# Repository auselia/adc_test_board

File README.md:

# ADS7057 test board (low-power 3.3 V version, v3)

The middle step between the perfboard and the AFE PCB. It takes the signal from the sensor, filters it, digitizes it with the ADS7057, and gives the SPI bus and two listener lines to a ZedBoard PMOD port. **It is powered only from the PMOD 3.3 V. There is no USB and no regulator.**

The 5 V / USB-C revision is kept in the git tag `v2-usb-5v`.

There are **two boards**, ordered separately:

| Board | What it is | Size |
|---|---|---|
| ADC test board (`ADC_Test`) | HPF, gain, LPF, driver, ADS7057, listener (WAKE_N, BIG_N), PMOD, bias-T for the head, current-measurement links, test points | **125 × 21.5 mm** |
| Sensor head (`ADC_Head`) | The perfboard charge amplifier on a PCB. The piezo wires solder to it. It is powered through the coax | 10 × 27 mm |

The head connects to **SENSOR IN (J1)** with one coax cable. The coax carries 3.3 V to the head (a bias-T) and the signal back. To use a function generator instead of the head, cut JP1.

The board is a narrow strip (21.5 mm) so that boards fit on adjacent PMOD ports (pitch about 22.7 mm). It is **always on**: the whole chain and the listener run all the time, and the listener only observes.

## What changed from v2 (5 V, USB-C)

| | v2 | v3 |
|---|---|---|
| Supply | USB-C or header, 5 V, SS14, ferrite, XC6206 for AVDD | **PMOD 3.3 V only**, through the 5-pin header J7 (jumper 1-2). AVDD through 10 Ω and 10 µF |
| Rails | 5 V, 2.3 V VMID5, 1.65 V VOCM | 3.3 V, **1.65 V** VMID5 and VOCM |
| Wake-up | LM393 window, trimmer RV1, nWAKE | **Listener**: passive 159 kHz high-pass, 723 kHz low-pass, two TLV7022 comparators. WAKE_N (35 mV) and BIG_N (111 mV) at SIG_IN, on PMOD pins 10 and 7. Observer only |
| Current measurement | none | J7: 4-wire source-measure unit connection (below). JP3 (capture rail) can be opened to measure or switch the chain alone |
| Test points | TP3 to TP20 on a bottom strip | TP3 to TP20 inside each block, names on the back |
| Size | 57 × 37.6 mm | 125 × 21.5 mm |
| Head | OPA365, 5 V from the coax | OPA365 at 3.3 V (V+ 2.9 V). Low-power option: OPA314 and Cf 220 pF on the same pads |

## Uses

The board serves two purposes. In the plant experiments, four boards sit on ZedBoard PMODs JA to JD: two control plants, one drying plant and one reference sensor. Each board is one channel. The listener lines tell the FPGA, next to the full waveform, how often a burst crosses a small or a large threshold. That data decides whether the battery product can run on a listener alone.

## Circuit

| Block | Parts | Values |
|---|---|---|
| High-pass filter | Sallen-Key, U1A | 100 pF C0G ×2, 10k, 20k: f0 = 113 kHz, Q = 0.71 |
| Gain | U1B | 1 + 3.9k/1k = 4.9 |
| Low-pass filter | Sallen-Key, U2A | 2.2k ×2, C1 = 2 × 100 pF, C2 = 100 pF: f0 = 512 kHz, Q = 0.71 |
| VMID5 (signal ground, half of +3V3_C, 1.65 V) | 10k/10k divider, U2B buffer | 10 Ω, 10 µF |
| Driver | THS4531, gain 1 | 1k in and feedback; VOCM = 1k/1k divider on AVDD |
| ADC input filter | | 10 Ω per leg, 4 × 100 pF C0G = 400 pF |
| AVDD (reference) | from +3V3_C through R34 10 Ω, C21 10 µF | 4.7 µF + 100 nF at the ADS7057 AVDD pin. RC corner 1.6 kHz |
| 3.3 V input | PMOD J3 pins 6 and 12 to J7 pin 1; J7 pins 2 and 3 are the board rail | C23 10 µF. No USB, no diode |
| Rail link | JP3 joins +3V3_C (U1, U2, U3, AVDD) to +3V3 (closed). The listener and DVDD are on +3V3 | Open JP3 to measure or switch the capture chain alone |
| MON output | 51 Ω from LPF_OUT to SMA J4 | The scope sees the same signal the ADC samples |
| Bias-T on SENSOR IN (J1) | JP1 (bridged), R26 47R + C32 10 µF, L2 470 µH, C33 100 nF, R27 1M | 3.3 V reaches the coax centre through 47 Ω and 470 µH. C33 passes the head signal to the filters |
| Listener filter | C40 100 pF + R35 10k (high-pass 159 kHz), R36 10k + C41 22 pF (low-pass 723 kHz) | Output LST, TP15. Gain 0.68 at 250 kHz (the filters load each other) |
| Listener thresholds | R21 1M, R22 33k, R39 15k, R40 15k, R41 33k, R23 1M from +3V3_L to ground; REFL = 1.65 V | WAKE_N ±24 mV and BIG_N ±76 mV at LST, which is 35 mV and 111 mV at SIG_IN (1.6 pC and 5.2 pC at Cf 47 pF) |
| Listener comparators | U6 (WAKE_N), U9 (BIG_N), TLV7022, 5 µA per channel, 260 ns | Open drain, 47k pull-ups R24 and R42 to 3.3 V |

Main board: 125 × 21.5 mm, 2 layers, all SMD parts on top, GND pour on both layers, 786 + 100 tracks.

### Sensor head

The perfboard circuit (TRL3 schematic), on its own board:

| Block | Parts | Values |
|---|---|---|
| Charge amplifier | U8 OPA365 (SOT-23-5) | 50 MHz, about 4.6 mA. Low-power option: OPA314 (3 MHz, 150 µA) with Cf 220 pF |
| Feedback | R28 1 MΩ, C34 47 pF C0G | Corner 3.4 kHz, gain 1/Cf |
| Reference | R29, R30 1M, C35 10 µF | VREF = V+/2, about 1.45 V |
| Output | R31 49.9 Ω, C38 100 nF | 50 Ω, AC-coupled onto the coax |
| Power from the coax | L1 470 µH, C36 100 nF, C37 10 µF | 3.3 V comes in on the coax centre. About 4.3 mA, V+ = 2.9 V |
| Piezo | TP1 (+, to the summing node), TP2 (−, to ground) | Two 1 mm holes. TP1 is on the centre line of the board and sets the piezo position |
| Output connector | J6 SMA, vertical | To SENSOR IN (J1) on the main board |

The bias-T at 3.3 V costs 0.17 dB at 250 kHz and 19 dB at 10 kHz (`python3 sim/head_bias_t.py 3.3`). The board is 22 mm long, not the 20 mm of the capsule drawing v3.

**Two head amplifiers.** The OPA365 is the lab default: it keeps the waveform faithful (noise gain 35 gives 1.4 MHz bandwidth) but draws 4.6 mA. The OPA314 draws 150 µA and fits the battery goal, but its 3 MHz gain-bandwidth needs Cf 220 pF (−3 dB near 360 kHz) and it has 14 nV/√Hz of noise against 4.5. Both are SOT-23-5 with the same pinout. Swap the amplifier and Cf.

## Silkscreen

| Label | What it is |
|---|---|
| SENSOR IN (J1) | SMA input for the sensor head. The centre pin carries 3.3 V while the jumper JP1 is bridged. Cut JP1 before you connect a function generator. |
| SCOPE OUT (J4) | SMA monitor output. It carries the same signal the ADC samples, through 51 Ω. Use a 1 MΩ scope input. A 50 Ω input halves the signal. |
| Test point names (back) | SIG_IN, HPF_OUT, GAIN_OUT, LPF_OUT, DRV_OUTP, DRV_OUTN, AINP, AINM, +3V3, AVDD, VMID5, VOCM, LST, WAKE_N, BIG_N, REFL, GND, GND |
| Silkscreen (top) | Test point numbers (TP3 to TP20) and IC numbers (U1 to U4, U6, U9); head: TP1, TP2, U8. Jumper names and PMOD pin legend on the back |
| PMOD pin list (back) | Pins used and their names |
| Leaf and waves (back) | Auselia mark |

Reference designators (R1, C4 and so on) are on the F.Fab layer, not on the silkscreen. Open the KiCad file to see them.

## Power

All power comes from the ZedBoard PMOD. J3 pins 6 and 12 carry 3.3 V and pins 5 and 11 carry GND. The ZedBoard feeds the PMOD connectors from its 3.3 V rail, rated 3 A and shared with the FMC and the other PMODs. This board draws about 27 mA, plus 5 mA for the head, so four boards are about 130 mA. Feed J7 instead (and cut JP6) to run on the bench.

J7 is a 5-pin header: 1 Onboard + (PMOD 3.3 V), 2 Force +, 3 Sense +, 4 Sense −, 5 Force −. Pins 2 and 3 are the board rail, pins 4 and 5 are ground. A jumper from pin 1 to pin 2 powers the board from the ZedBoard. To power it from a source-measure unit (for example a Keysight B2901BL) remove the jumper and connect Force to pins 2 and 5 and Sense to pins 3 and 4. The SMU then measures the total board current. JP3 (closed) joins the capture rail: open it to feed or switch U1, U2, U3 and AVDD separately. JP1 is the head power link.

AVDD is the ADC reference, and full scale is ±AVDD. It comes from the rail through 10 Ω and 10 µF. The ZedBoard 3.3 V noise is not known yet: probe TP11 and TP12.

The long-term product runs from a battery for a year. This board is the lab version. The listener (about 25 µA) and the OPA314 head (150 µA) are the building blocks for that, and the plan is in `doc/lowpower_plan.md`.

## Through-hole parts

JLCPCB solders these. They are in the BOM and the pick-and-place file.

| Ref | Part | LCSC |
|---|---|---|
| J1, J4 (and J6 on the head) | SMA jack, vertical, 5 pins (sensor in, MON, head out) | C496549 |
| J7 | 1×5 pin header, 2.54 mm (power / source-measure unit) | C492404 |
| J3 | 2×6 right-angle pin header, 2.54 mm | C60565 |

If JLCPCB declines a through-hole part, delete its line from the BOM and solder it yourself. The board has the same footprints either way.

## Connectors

- **J1 SENSOR IN:** SMA for the sensor head, carries +3.3 V on the centre pin (JP1 bridged).
- **J4 SCOPE OUT:** SMA monitor output, LPF_OUT through 51 Ω.
- **J7 header:** power and 4-wire SMU connection (jumper 1-2 for the PMOD supply).
- **H1, H2:** M3 mounting holes.
- **J3 PMOD:** 1 CS, 3 SDO, 4 SCLK, 5/11 GND, 6/12 3V3, 7 BIG_N, 10 WAKE_N.

All device ports are SMA female. Use one cable type everywhere (SMA male to male, RG316 or RG174, short): head to SENSOR IN, SENSOR IN to a generator, SCOPE OUT to the oscilloscope through an SMA male to BNC female adapter. The RP-SMA parts in some shops do not mate with these jacks. Connect the head to the oscilloscope only through the board, since the bias-T that powers the head is on the board.

Before you plug the board into JA–JD, check that pins 5/6 and 11/12 line up with GND/VCC on the ZedBoard silkscreen. Adjacent ports are about 22.7 mm apart and the board is 21.5 mm wide.

## SPI

- CS falling edge starts a conversion.
- Read 18 SCLK cycles on SDO. The frame is a leading 0, then D13..D0, then zeros (datasheet Fig. 1).
- Each frame returns the result of the **previous** conversion. The first frame after power-up returns all zeros.
- After power-up, send **24 SCLKs** in the first frame. That starts the offset calibration (datasheet 8.4.3.1), and SDO stays at zero. Then wait at least 95 ns before the next CS fall.
- Repeat the calibration when AVDD or the temperature changes a lot.
- SCLK can go up to 60 MHz. Start at 10–20 MHz.

## Cost (JLCPCB Economic PCBA, shipped to Chile)

The two boards are two JLCPCB orders (or one checkout with two designs). `python3 hw/tools/cost.py` prints the model. It is calibrated on the real quote of the first revision (2026-10-12, 5 boards, $114.36, no bias-T). The new parts have list prices from the JLCPCB library of 2026-10-15. The v2 numbers are estimates until you upload the files.

| Order | Goods (parts + PCB + fees) | Parts | Fees |
|---|---|---|---|
| ADC board × 2 | $66.84 | $32.20 | $30.64 |
| ADC board × 3 | $83.83 | $48.30 | $31.54 |
| ADC board × 5 | $117.82 | $80.50 | $33.33 |
| Sensor head × 5 | $40.77 | $15.65 | $21.12 |
| Sensor head × 10 | $57.94 | $31.29 | $22.65 |

Both orders together, with shipping (Global Standard $10.75 per parcel) and 19 % IVA:

| | One parcel | Two parcels |
|---|---|---|
| 2 ADC boards + 5 heads | $140.84 | $153.64 |
| 2 ADC boards + 10 heads | $161.46 | $174.26 |

- The head's fixed fees (setup $8.24, stencil $1.55, hand-solder labor $3.61, PCB $4.00, one more extended type) are about $20 per order. A single panel would save them, but it forces equal quantities and mouse-bite tabs. Two orders let you buy 2 ADC boards and 10 heads.
- The OPA365 ($2.67) is the most expensive part of a head. The OPA2365 (SOIC-8) would be $1.38 and needs no new extended fee, but it does not fit in 10 mm × 27 mm with the SMA.
- DHL Express costs about $32 more per parcel (3–7 days).
- "Confirm Parts Placement" adds $0.45 per order.

First revision, real quote for 5 boards (no head, no bias-T):

| Item | Price |
|---|---|
| PCB, 5 pcs, 2 layers, HASL with lead, 24 h build | $4.00 |
| Components, 27 part types | $80.14 |
| Setup fee | $8.24 |
| Stencil | $1.55 |
| Extended components fee, 4 types | $12.36 |
| SMT assembly | $1.32 |
| Hand-soldering labor | $3.61 |
| Manual assembly, through-hole joints | $2.23 |
| Nitrogen reflow | $0.91 |
| **Order total** | **$114.36** |

The ADS7057 pays no X-ray fee in Economic assembly. The through-hole part types (SMA, headers, trimmer) pay no extended-part fee.

> The model is calibrated on the first quote. A real quote of this revision (2026-10-15, 5 ADC boards, 5 heads, one checkout) showed merchandise $159.73 and shipping $52.45 because the cart was above $150. Split it in two orders (Global Standard $10.75 each) to stay below that line.

## JLCPCB placement check

The JLCPCB viewer showed four problems on the first revision, and the CPL corrects them. **New parts are not checked yet:** U6 and U9 (TLV7022, SOT-23-8), U8 (SOT-23-5, head), L1 and L2 (1210 inductors), J6 (SMA). Look at them in the viewer.

| Part | Problem | CPL rotation |
|---|---|---|
| J7 (1×5 header) | Rotation as in the CPL (90), not checked in the viewer | check |
| J3 (2×6 header) | Row horizontal, pads vertical | 0 → 90 |

J3 and J7 have their origin on pin 1 in the KiCad footprint, so they are placed by that pin.

## Verification

| Check | Status | Result |
|---|---|---|
| ERC, DRC, schematic-to-board parity | Done | 0 errors, 0 unconnected, 0 mismatches |
| Pinouts and polarity against the datasheets | Done | All ICs, SS14 |
| JLCPCB placement viewer | **Open** for U6, U9, U8, L1, L2, J6 | 2 rotations fixed. Check again after the new CPL |
| DC bias, AC response, noise | Done | Table below |
| Tolerance Monte Carlo, 150 runs | Done | 10 kHz loss under 40 dB in 11 of 150 runs |
| 250 kHz burst, headroom at 3.3 V | Done | A 120 mV event reaches 16 % of full scale. Clipping starts near 0.37 V (`doc/data/sim.json`) |
| As-built netlist, rails to listener | Done | `python3 sim/netlist_verify.py`: 18 DC checks, gains and bursts all pass. It found that the first listener filter passed only 0.45 of the signal, which was fixed (R36, C41, R39, R40) |
| Listener on 25 real captures | Done | 7 of 7 events above WAKE_N, none of the 18 noise captures (peak 26 mV against 35 mV). Rate of false alarms per hour is open (`sim/g1_listener.py`) |
| ADC input settling | Done | 30 to 55 ns against 95 ns minimum |
| Cable on the SCOPE OUT SMA | Done | No peaking up to 5 nF |
| THS4531 into 10 Ω and 400 pF | **Open** | TI's model fails in ngspice and LTspice batch mode does not run here. `sim/ths4531_stability_estimate.py` gives 48 to 77° of margin for assumed output impedances. Run `sim/ltspice/ths4531_cap_load.cir` in LTspice |
| Head and bias-T, ngspice with the OPA365 model | Done | 0.17 dB loss at 250 kHz, 19 dB at 10 kHz, about 4.3 mA at 3.3 V. `python3 sim/head_bias_t.py 3.3` |
| ZedBoard 3.3 V rail noise | **Open** | Probe TP11 and TP12 with the board plugged in |
| Adjacent PMOD ports (22.7 mm) | **Open** | Print 1:1 and test |
| Head board, DRC | Done | 0 unconnected, no electrical errors. Two courtyard overlaps (TP/L1 and C34/R28) |
| Head: piezo wires, strain relief, RTV | Open | Mechanical, on the bench |
| Print the PCB 1:1 and test-fit parts | Open | |
| Fit on the ZedBoard PMOD | Open | |
| Bench bring-up | Open | See below |

`sim/vendor_chain.py` runs the checks and `sim/vendor_results.txt` holds the output. The OPA365 is TI's own model. The THS4531 is a datasheet-based model (27 MHz, 2.5 Ω), because TI's model gives a −3 dB point at 17 kHz in ngspice. The ADC input is the datasheet model: 50 Ω and 16 pF per leg. Run `python3 sim/models/fetch_models.py` to download the TI models, which are not stored in the repo.

| Result | Value | Target |
|---|---|---|
| DC points | VMID5 1.65 V, VOCM 1.65 V, ADC inputs 1.65 V | |
| Gain at 250 kHz, SMA to ADC | 12.2 dB (×4.1) | |
| Flatness 230 to 280 kHz | 0.08 dB | < 1 dB |
| Loss at 10 kHz, re 250 kHz | 40.5 dB, worst of 150 runs 39.7 dB | ≥ 40 dB |
| Loss at 2 MHz | 24.0 dB | ≥ 20 dB |
| −3 dB band | 106 to 502 kHz | |
| Board noise at the ADC | 77 µV rms, 0.2 LSB | |

Things the simulation does not cover:

- THS4531 stability with the 400 pF load. TI's guidance is a 2 pF differential load without an isolation resistor, so 20 Ω and 400 pF needs a measurement. If it rings, raise R16 and R17 from 10 Ω to 20 or 30 Ω.
- Temperature and the noise of a real power bank.
- Layout coupling and the real ZedBoard supply.

Paper checks:

- The chain was simulated at 3.3 V (`sim/vendor_chain.py`, `sim/g1_chain33.py`).
- The board draws about 27 mA plus 5 mA for the head, about 0.1 W.

## Bring-up

With the sensor head: connect it to J1 with the coax, power the board from the PMOD (or J7 at 3.3 V), and the head runs from the rail (about +4.3 mA). Measure about 2.9 V on C37 and 1.45 V on the OPA365 output, VREF and C35. Then continue from step 3.

1. Remove the J7 jumper and feed pins 2 and 5 with 3.3 V and a 100 mA limit (SMU Force), Sense on pins 3 and 4. Check +3V3 (3.30 V), AVDD (3.30 V), VOCM (1.65 V), VMID5 (1.65 V) and REFL (1.65 V) at the test points before the PMOD connects. Then fit the jumper 1-2 and connect the PMOD.
2. Plug the board into the ZedBoard and check that WAKE_N and BIG_N read high (3.3 V).
3. Feed J1 from the Analog Discovery 2 with a 250 kHz, 100 mV sine. Compare SCOPE OUT with the input on the scope (1 MΩ input).
4. Read SPI codes. Check the idle code and the amplitude against the scope.
5. Sweep 10 kHz to 2 MHz and compare with the table above. The 10 kHz loss is the thinnest margin.
6. Raise a 250 kHz burst from 10 mV: WAKE_N must drop near 35 mV and BIG_N near 111 mV at J1 (±12 mV from the comparator offset). Log TP15 to TP18 on the scope.
7. With the SMU on J7, read the total current (about 25 mA). Open JP3 to read the capture chain and the listener separately.

## Manual (`doc/`)

`doc/ADS7057_test_board_hardware_manual_letter_v0.3.pdf` explains the boards in 54 steps plus the sensor head: the basics, every block, the layout, the order and the bring-up. Two print versions (`_print`, `_print_duplex`) have a 14 mm binding margin.

Rebuild: `M4_PDF_PYTHON=<python with pymupdf> python3 doc/tools/make_adc_manual.py`. The figures read `doc/data/board.json` and `doc/data/sim.json`, made by `doc/tools/export_board.py` (KiCad python) and `doc/tools/export_sim.py`.

## Files (`hw/`)

- `ADC_Test.kicad_pro/.kicad_sch`: the KiCad 10 project and the schematic of both boards.
- `ADC_Test.kicad_pcb`: main board. `ADC_Head.kicad_pcb`: sensor head. Both are built from the same netlist.
- `ADC_Test_schematic.pdf`: the schematic.
- `fab/ADC_Test_gerbers.zip`, `fab/ADC_Head_gerbers.zip`: Gerbers and drill files.
- `fab/ADC_*_BOM_JLC.csv` and `fab/ADC_*_CPL_JLC.csv`: BOM and pick-and-place for each board.
- `preview/`: renders and the 1:1 print PDFs of both boards.
- DRC: main board 0 errors and 0 unconnected (the parity warnings are the head parts, which are not on this board). Head board 0 unconnected, two courtyard warnings.

## Rebuild

```
python3 hw/tools/design.py hw          # schematic (then export netlist with kicad-cli)
NOPLANE=1 FREEROUTING=/path/to/freerouting hw/tools/route.sh 60   # place (layout_v3.py), route, finish
BOARD=head FREEROUTING=/path/to/freerouting hw/tools/route.sh 60   # the sensor head
hw/tools/drc.sh; BOARD=head hw/tools/drc.sh
hw/tools/fab.sh && BOARD=adc python3 hw/tools/jlc_files.py && BOARD=head python3 hw/tools/jlc_files.py
```

Freerouting 2.4.1 needs Java 25 (the macOS .dmg bundles it).

## At JLCPCB checkout

- Two orders: upload `ADC_Test_*` and `ADC_Head_*` separately.
- Upload the new CPL, then open Component Placements and check U6, U9 (pin 1), J7 and J3 (see "JLCPCB placement check"). On the head also check U8 pin 1, L1, J6.
- Look at J1, J4 and J6 as well. The SMA model looked offset against its four legs.
- Check pin 1 of U4 (ADS7057) in particular.

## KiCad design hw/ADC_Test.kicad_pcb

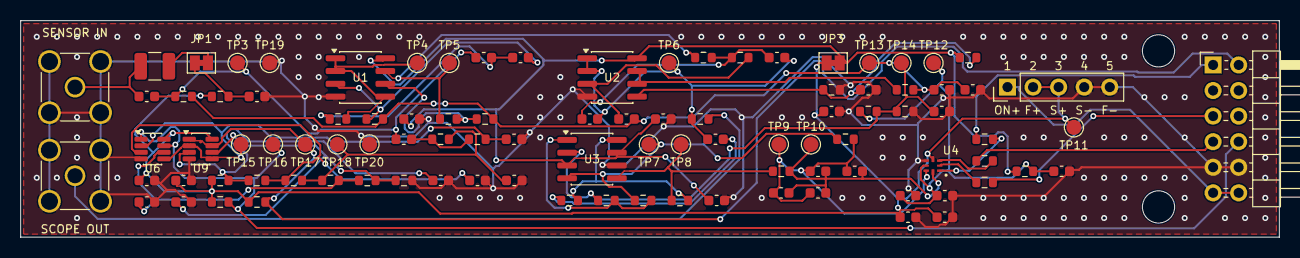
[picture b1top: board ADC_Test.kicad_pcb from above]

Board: 2 copper layers, 125.0 x 21.5 mm, 101 parts (0 on the bottom side), 44 nets.

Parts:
C1, C2, C4, C5, C6, C14, C15, C16, C17, C40: 100pF C0G; C_0603_1608Metric
C3, C9, C10, C12, C20, C22, C26, C27, C28, C33, C43, C44, C45: 100nF; C_0603_1608Metric
C7, C11, C13, C19, C42: 1uF; C_0603_1608Metric
C8, C21, C23, C32: 10uF; C_0603_1608Metric
C18: 4.7uF; C_0603_1608Metric
C41: 22pF C0G; C_0603_1608Metric
H1, H2: M3; MountingHole_3.2mm_M3
J1: SMA SENSOR IN; SMA_Amphenol_132134-11_Vertical
J3: PMOD (ZedBoard); PinHeader_2x06_P2.54mm_Horizontal
J4: SMA MON; SMA_Amphenol_132134-11_Vertical
J7: POWER / SMU; PinHeader_1x05_P2.54mm_Vertical
JP1: HEAD PWR; SolderJumper-2_P1.3mm_Bridged_Pad1.0x1.5mm
JP3: CAPTURE LINK; SolderJumper-2_P1.3mm_Bridged_Pad1.0x1.5mm
L2: 470uH; L_1210_3225Metric
R1, R7, R8, R35, R36: 10k; R_0603_1608Metric
R2: 20k; R_0603_1608Metric
R3: 3.9k; R_0603_1608Metric
R4, R10, R11, R12, R13, R14, R15: 1.00k; R_0603_1608Metric
R5, R6: 2.2k; R_0603_1608Metric
R9, R16, R17, R34: 10R; R_0603_1608Metric
R18, R19, R20: 22R; R_0603_1608Metric
R21, R23, R27: 1M; R_0603_1608Metric
R22, R41: 33k; R_0603_1608Metric
R24, R42: 47k; R_0603_1608Metric
R25: 51R; R_0603_1608Metric
R26: 47R; R_0603_1608Metric
R39, R40: 15k; R_0603_1608Metric
TP3: SIG_IN; TestPoint_Pad_D1.5mm
TP4: HPF_OUT; TestPoint_Pad_D1.5mm
TP5: GAIN_OUT; TestPoint_Pad_D1.5mm
TP6: LPF_OUT; TestPoint_Pad_D1.5mm
TP7: DRV_OUTP; TestPoint_Pad_D1.5mm
TP8: DRV_OUTN; TestPoint_Pad_D1.5mm
TP9: AINP; TestPoint_Pad_D1.5mm
TP10: AINM; TestPoint_Pad_D1.5mm
TP11: +3V3; TestPoint_Pad_D1.5mm
TP12: AVDD; TestPoint_Pad_D1.5mm
TP13: VMID5; TestPoint_Pad_D1.5mm
TP14: VOCM; TestPoint_Pad_D1.5mm
TP15: LST; TestPoint_Pad_D1.5mm
TP16: WAKE_N; TestPoint_Pad_D1.5mm
TP17: BIG_N; TestPoint_Pad_D1.5mm
TP18: REFL; TestPoint_Pad_D1.5mm
TP19, TP20: GND; TestPoint_Pad_D1.5mm
U1, U2: OPA2365; SOIC-8_3.9x4.9mm_P1.27mm
U3: THS4531; SOIC-8_3.9x4.9mm_P1.27mm
U4: ADS7057; ADS7057_X2QFN-8_1.5x1.5mm
U6, U9: TLV7022; SOT-23-8

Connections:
+3V3: C19.1, C20.1, C23.1, C28.1, C45.1, J7.2, J7.3, JP3.1, R21.1, R24.1, R26.1, R42.1, TP11.1, U4.4, U6.8, U9.8
+3V3_C: C3.1, C10.1, C12.1, JP3.2, R7.1, R34.1, U1.8, U2.8, U3.3, U3.7
+3V3_PMOD: J3.11, J3.12, J7.1
AINM: C14.2, C15.2, C16.2, C17.2, R17.2, TP10.1, U4.8
AINP: C14.1, C15.1, C16.1, C17.1, R16.2, TP9.1, U4.7
AVDD: C18.1, C21.1, C22.1, R14.1, R34.2, TP12.1, U4.6
BIG_N: J3.2, R42.2, TP17.1, U9.1, U9.7
CS: J3.1, R18.1
CS_A: R18.2, U4.1
DRV_A: C11.2, R10.1
DRV_INN: R11.2, R12.2, U3.1
DRV_INP: R10.2, R13.2, U3.8
DRV_OUTN: R13.1, R17.1, TP8.1, U3.5
DRV_OUTP: R12.1, R16.1, TP7.1, U3.4
GAIN_OUT: R3.1, R5.1, TP5.1, U1.7
GND: C3.2, C7.2, C8.2, C9.2, C10.2, C12.2, C13.2, C18.2, C19.2, C20.2, C21.2, C22.2, C23.2, C26.2, C27.2, C28.2, C32.2, C41.2, C42.2, C43.2, C44.2, C45.2, J1.2, J3.9, J3.10, J4.2, J7.4, J7.5, R8.2, R15.2, R23.2, TP19.1, TP20.1, U1.4, U2.4, U3.6, U4.5, U6.4, U9.4
GN_FB: R3.2, R4.1, U1.6
HEAD_LINE: C33.1, J1.1, L2.1
HEAD_PWR: C32.1, JP1.1, R26.2
HEAD_PWR_L: JP1.2, L2.2
HPF_OUT: R1.2, TP4.1, U1.1, U1.2, U1.5
HP_A: C1.2, C2.1, R1.1
HP_B: C2.2, R2.1, U1.3
LPF_OUT: C4.2, C5.2, C11.1, R25.1, TP6.1, U2.1, U2.2
LP_A: C4.1, C5.1, R5.2, R6.1
LP_B: C6.1, R6.2, U2.3
LST: C41.1, R36.2, TP15.1, U6.2, U6.5, U9.2, U9.5
LST_A: C40.2, R35.1, R36.1
MON: J4.1, R25.2
REFL: C42.1, R35.2, R39.2, R40.1, TP18.1
SCLK: J3.7, R19.1
SCLK_A: R19.2, U4.3
SDO: J3.5, R20.2
SDO_A: R20.1, U4.2
SIG_IN: C1.1, C33.2, C40.1, R27.1, TP3.1
TH1M: C27.1, R40.2, R41.1, U6.6
TH1P: C26.1, R22.2, R39.1, U6.3
TH2M: C44.1, R23.1, R41.2, U9.6
TH2P: C43.1, R21.2, R22.1, U9.3
VMID5: C6.2, C8.1, C9.1, R2.2, R4.2, R9.2, R27.2, TP13.1
VMID_BUF: R9.1, U2.6, U2.7
VMID_DIV: C7.1, R7.2, R8.1, U2.5
VOCM: C13.1, R11.1, R14.2, R15.1, TP14.1, U3.2
WAKE_N: J3.8, R24.2, TP16.1, U6.1, U6.7

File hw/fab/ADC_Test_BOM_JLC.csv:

Comment,Designator,Footprint,LCSC Part #
100pF C0G,"C1,C2,C4,C5,C6,C14,C15,C16,C17,C40",C_0603_1608Metric,C14858
100nF,"C3,C9,C10,C12,C20,C22,C26,C27,C28,C33,C43,C44,C45",C_0603_1608Metric,C14663
1uF,"C7,C11,C13,C19,C42",C_0603_1608Metric,C15849
10uF,"C8,C21,C23,C32",C_0603_1608Metric,C19702
4.7uF,C18,C_0603_1608Metric,C19666
22pF C0G,C41,C_0603_1608Metric,C1653
SMA jack,"J1,J4",SMA_Amphenol_132134-11_Vertical,C496549
Header 2x6 right angle,J3,PinHeader_2x06_P2.54mm_Horizontal,C60565
Header 1x5,J7,PinHeader_1x05_P2.54mm_Vertical,C492404
470uH,L2,L_1210_3225Metric,C75644
10k,"R1,R7,R8,R35,R36",R_0603_1608Metric,C25804
20k,R2,R_0603_1608Metric,C4184
3.9k,R3,R_0603_1608Metric,C23018
1.00k,"R4,R10,R11,R12,R13,R14,R15",R_0603_1608Metric,C21190
2.2k,"R5,R6",R_0603_1608Metric,C4190
10R,"R9,R16,R17,R34",R_0603_1608Metric,C22859
22R,"R18,R19,R20",R_0603_1608Metric,C23345
1M,"R21,R23,R27",R_0603_1608Metric,C22935
33k,"R22,R41",R_0603_1608Metric,C4216
47k,"R24,R42",R_0603_1608Metric,C25819
51R,R25,R_0603_1608Metric,C23197
47R,R26,R_0603_1608Metric,C23182
15k,"R39,R40",R_0603_1608Metric,C22809
OPA2365,"U1,U2",SOIC-8_3.9x4.9mm_P1.27mm,C130011
THS4531,U3,SOIC-8_3.9x4.9mm_P1.27mm,C705347
ADS7057,U4,ADS7057_X2QFN-8_1.5x1.5mm,C2669902
TLV7022,"U6,U9",SOT-23-8,C2862588

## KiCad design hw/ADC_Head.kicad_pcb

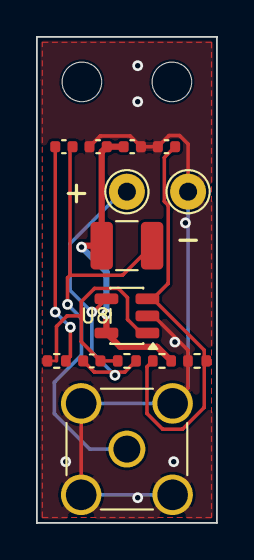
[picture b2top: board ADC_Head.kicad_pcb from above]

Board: 2 copper layers, 10.0 x 27.0 mm, 16 parts (0 on the bottom side), 7 nets.

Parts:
C34: 47pF C0G; C_0402_1005Metric
C35, C37: 10uF; C_0402_1005Metric
C36, C38: 100nF; C_0402_1005Metric
H3, H4: M2; MountingHole_2.2mm_M2
J6: SMA HEAD OUT; SMA_Amphenol_132134-11_Vertical
L1: 470uH; L_1210_3225Metric
R28, R29, R30: 1M; R_0402_1005Metric
R31: 49.9R; R_0402_1005Metric
TP1: PIEZO +; TestPoint_THTPad_D2.0mm_Drill1.0mm
TP2: PIEZO -; TestPoint_THTPad_D2.0mm_Drill1.0mm
U8: OPA365; SOT-23-5

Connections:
HAC: C38.1, R31.2
HGND: C35.2, C36.2, C37.2, J6.2, R30.2, TP2.1, U8.2
HLINE: C38.2, J6.1, L1.1
HOUT: C34.2, R28.2, R31.1, U8.1
HREF: C35.1, R29.2, R30.1, U8.3
HSUM: C34.1, R28.1, TP1.1, U8.4
HV: C36.1, C37.1, L1.2, R29.1, U8.5

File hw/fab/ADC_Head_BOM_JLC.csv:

Comment,Designator,Footprint,LCSC Part #
47pF C0G,C34,C_0402_1005Metric,C1567
10uF,"C35,C37",C_0402_1005Metric,C15525
100nF,"C36,C38",C_0402_1005Metric,C307331
SMA jack,J6,SMA_Amphenol_132134-11_Vertical,C496549
470uH,L1,L_1210_3225Metric,C75644
1M,"R28,R29,R30",R_0402_1005Metric,C26083
49.9R,R31,R_0402_1005Metric,C25120
OPA365,U8,SOT-23-5,C96626

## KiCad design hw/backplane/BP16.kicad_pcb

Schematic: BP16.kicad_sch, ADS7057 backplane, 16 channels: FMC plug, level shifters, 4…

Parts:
C1, C2, C3, C4, C5, C6, C7, C8, C9, C10, C11, C12, C13, C14, C15, C16, C18, C20, C22, C24, C26, C28, C30, C32, C34, C36, C38, C40, C42, C44, C46, C48, C50, C51, C52, C54, C58: 100nF; C_0603_1608Metric; LCSC C14663
C17, C19, C21, C23, C25, C27, C29, C31, C33, C35, C37, C39, C41, C43, C45, C47, C49: 10uF; C_0603_1608Metric; LCSC C19702
C53, C55, C56, C57: 22uF 25V; C_0805_2012Metric; LCSC C45783
C59, C60: 10nF; C_0603_1608Metric; LCSC C57112
D1: SS14; D_SMA; LCSC C2480
D2: 3V3 OK; LED_0603_1608Metric; LCSC C2286
H1, H2, H3, H4, H5, H6: M3; MountingHole_3.2mm_M3
J1: ASP-134602-01; ASP-134602-01_LPC; LCSC C2875619
J2: SLOT 0; PinSocket_2x06_P2.54mm_Vertical; LCSC C36191
J3: SLOT 1; PinSocket_2x06_P2.54mm_Vertical; LCSC C36191
J4: SLOT 2; PinSocket_2x06_P2.54mm_Vertical; LCSC C36191
J5: SLOT 3; PinSocket_2x06_P2.54mm_Vertical; LCSC C36191
J6: SLOT 4; PinSocket_2x06_P2.54mm_Vertical; LCSC C36191
J7: SLOT 5; PinSocket_2x06_P2.54mm_Vertical; LCSC C36191
J8: SLOT 6; PinSocket_2x06_P2.54mm_Vertical; LCSC C36191
J9: SLOT 7; PinSocket_2x06_P2.54mm_Vertical; LCSC C36191
J10: SLOT 8; PinSocket_2x06_P2.54mm_Vertical; LCSC C36191
J11: SLOT 9; PinSocket_2x06_P2.54mm_Vertical; LCSC C36191
J12: SLOT 10; PinSocket_2x06_P2.54mm_Vertical; LCSC C36191
J13: SLOT 11; PinSocket_2x06_P2.54mm_Vertical; LCSC C36191
J14: SLOT 12; PinSocket_2x06_P2.54mm_Vertical; LCSC C36191
J15: SLOT 13; PinSocket_2x06_P2.54mm_Vertical; LCSC C36191
J16: SLOT 14; PinSocket_2x06_P2.54mm_Vertical; LCSC C36191
J17: SLOT 15; PinSocket_2x06_P2.54mm_Vertical; LCSC C36191
J18: 5 V IN; TerminalBlock_Phoenix_MKDS-1,5-2-5.08_1x02_P5.08mm_Horizont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; LCSC C8465
R1, R2, R3, R4, R5, R6, R7, R8, R9, R10, R11, R12, R13, R14, R15, R16, R17, R18, R19, R20, R21, R22, R23, R24, R25, R26, R27, R28, R29, R30, R31, R32, R33, R34, R35, R36, R37, R38, R39, R40, R41, R42, R43, R44, R45, R46, R47, R48, R49, R50, R51, R52, R53, R54, R55, R56: 100k; R_0603_1608Metric; LCSC C25803
R57, R58, R59, R60, R61, R62, R63, R64, R65, R66, R67, R68, R69, R70, R71, R72: 22R; R_0603_1608Metric; LCSC C23345
R73: 1k; R_0603_1608Metric; LCSC C21190
TP1: +3V3; TestPoint_Pad_D1.5mm
TP2: GND; TestPoint_Pad_D1.5mm
TP3: +5V; TestPoint_Pad_D1.5mm
TP4: VADJ; TestPoint_Pad_D1.5mm
U1, U2, U3, U4, U5, U6, U7, U8: SN74LVC8T245; TSSOP-24_4.4x7.8mm_P0.65mm; LCSC C27643
U9, U10: SN74LVC244A; TSSOP-20_4.4x6.5mm_P0.65mm; LCSC C7668
U11: TPS7A8300; QFN-20-1EP_3.5x3.5mm_P0.5mm_EP2x2mm; LCSC C544500

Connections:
+3V3: C2.1, C4.1, C6.1, C8.1, C10.1, C12.1, C14.1, C16.1, C19.1, C20.1, C21.1, C22.1, C23.1, C24.1, C25.1, C26.1, C27.1, C28.1, C29.1, C30.1, C31.1, C32.1, C33.1, C34.1, C35.1, C36.1, C37.1, C38.1, C39.1, C40.1, C41.1, C42.1, C43.1, C44.1, C45.1, C46.1, C47.1, C48.1, C49.1, C50.1, C51.1, C52.1, C55.1, C56.1, C57.1, C58.1, C60.1, J2.11, J2.12, J3.11, J3.12, J4.11, J4.12, J5.11, J5.12, J6.11, J6.12, J7.11, J7.12, J8.11, J8.12, J9.11, J9.12, J10.11, J10.12, J11.11, J11.12, J12.11, J12.12, J13.11, J13.12, J14.11, J14.12, J15.11, J15.12, J16.11, J16.12, J17.11, J17.12, R9.1, R10.1, R11.1, R12.1, R13.1, R14.1, R15.1, R16.1, R17.1, R18.1, R19.1, R20.1, R21.1, R22.1, R23.1, R24.1, R25.1, R26.1, R27.1, R28.1, R29.1, R30.1, R31.1, R32.1, R33.1, R34.1, R35.1, R36.1, R37.1, R38.1, R39.1, R40.1, R41.1, R42.1, R43.1, R44.1, R45.1, R46.1, R47.1, R48.1, R49.1, R50.1, R51.1, R52.1, R53.1, R54.1, R55.1, R56.1, R73.1, TP1.1, U1.23 (VCCB), U1.24 (VCCB), U2.23 (VCCB), U2.24 (VCCB), U3.23 (VCCB), U3.24 (VCCB), U4.23 (VCCB), U4.24 (VCCB), U5.23 (VCCB), U5.24 (VCCB), U6.23 (VCCB), U6.24 (VCCB), U7.23 (VCCB), U7.24 (VCCB), U8.23 (VCCB), U8.24 (VCCB), U9.20 (VCC), U10.20 (VCC), U11.1 (OUT), U11.2 (SNS), U11.19 (OUT), U11.20 (OUT)
+5V: C53.1, C54.1, D1.1 (K), TP3.1, U11.14 (EN), U11.15 (IN), U11.16 (IN), U11.17 (IN)
+5V_IN: D1.2 (A), J18.1
BIG0: J2.1, R11.2, U3.21 (B1)
BIG1: J3.1, R14.2, U3.20 (B2)
BIG2: J4.1, R17.2, U3.19 (B3)
BIG3: J5.1, R20.2, U3.18 (B4)
BIG4: J6.1, R23.2, U3.17 (B5)
BIG5: J7.1, R26.2, U3.16 (B6)
BIG6: J8.1, R29.2, U3.15 (B7)
BIG7: J9.1, R32.2, U3.14 (B8)
BIG8: J10.1, R35.2, U6.21 (B1)
BIG9: J11.1, R38.2, U6.20 (B2)
BIG10: J12.1, R41.2, U6.19 (B3)
BIG11: J13.1, R44.2, U6.18 (B4)
BIG12: J14.1, R47.2, U6.17 (B5)
BIG13: J15.1, R50.2, U6.16 (B6)
BIG14: J16.1, R53.2, U6.15 (B7)
BIG15: J17.1, R56.2, U6.14 (B8)
CS0: J2.2, R9.2, U1.21 (B1)
CS1: J3.2, R12.2, U1.20 (B2)
CS2: J4.2, R15.2, U1.19 (B3)
CS3: J5.2, R18.2, U1.18 (B4)
CS4: J6.2, R21.2, U1.17 (B5)
CS5: J7.2, R24.2, U1.16 (B6)
CS6: J8.2, R27.2, U1.15 (B7)
CS7: J9.2, R30.2, U1.14 (B8)
CS8: J10.2, R33.2, U4.21 (B1)
CS9: J11.2, R36.2, U4.20 (B2)
CS10: J12.2, R39.2, U4.19 (B3)
CS11: J13.2, R42.2, U4.18 (B4)
CS12: J14.2, R45.2, U4.17 (B5)
CS13: J15.2, R48.2, U4.16 (B6)
CS14: J16.2, R51.2, U4.15 (B7)
CS15: J17.2, R54.2, U4.14 (B8)
FB: C60.2, U11.3 (FB)
LA00_N_CC: J1.G7 (LA00_N_CC), U4.4 (A2)
LA00_P_CC: J1.G6 (LA00_P_CC), U4.3 (A1)
LA01_N_CC: J1.D9 (LA01_N_CC), U1.4 (A2)
LA01_P_CC: J1.D8 (LA01_P_CC), U1.3 (A1)
LA02_N: J1.H8 (LA02_N), U4.6 (A4)
LA02_P: J1.H7 (LA02_P), U4.5 (A3)
LA03_N: J1.G10 (LA03_N), U4.8 (A6)
LA03_P: J1.G9 (LA03_P), U4.7 (A5)
LA04_N: J1.H11 (LA04_N), U4.10 (A8)
LA04_P: J1.H10 (LA04_P), U4.9 (A7)
LA05_N: J1.D12 (LA05_N), U1.8 (A6)
LA05_P: J1.D11 (LA05_P), U1.7 (A5)
LA06_N: J1.C11 (LA06_N), U1.6 (A4)
LA06_P: J1.C10 (LA06_P), U1.5 (A3)
LA07_N: J1.H14 (LA07_N), U5.6 (A4)
LA07_P: J1.H13 (LA07_P), U5.5 (A3)
LA08_N: J1.G13 (LA08_N), U5.4 (A2)
LA08_P: J1.G12 (LA08_P), U5.3 (A1)
LA09_N: J1.D15 (LA09_N), U2.4 (A2)
LA09_P: J1.D14 (LA09_P), U1.10 (A8)
LA10_N: J1.C15 (LA10_N), U2.3 (A1)
LA10_P: J1.C14 (LA10_P), U1.9 (A7)
LA11_N: J1.H17 (LA11_N), U5.10 (A8)
LA11_P: J1.H16 (LA11_P), U5.9 (A7)
LA12_N: J1.G16 (LA12_N), U5.8 (A6)
LA12_P: J1.G15 (LA12_P), U5.7 (A5)
LA13_N: J1.D18 (LA13_N), U2.7 (A5)
LA13_P: J1.D17 (LA13_P), U2.5 (A3)
LA14_N: J1.C19 (LA14_N), U2.8 (A6)
LA14_P: J1.C18 (LA14_P), U2.6 (A4)
LA15_N: J1.H20 (LA15_N), U6.6 (A4)
LA15_P: J1.H19 (LA15_P), U6.5 (A3)
LA16_N: J1.G19 (LA16_N), U6.4 (A2)
LA16_P: J1.G18 (LA16_P), U6.3 (A1)
LA17_N_CC: J1.D21 (LA17_N_CC), U2.10 (A8)
LA17_P_CC: J1.D20 (LA17_P_CC), U2.9 (A7)
LA18_N_CC: J1.C23 (LA18_N_CC), U3.4 (A2)
LA18_P_CC: J1.C22 (LA18_P_CC), U3.3 (A1)
LA19_N: J1.H23 (LA19_N), U6.10 (A8)
LA19_P: J1.H22 (LA19_P), U6.9 (A7)
LA20_N: J1.G22 (LA20_N), U6.8 (A6)
LA20_P: J1.G21 (LA20_P), U6.7 (A5)
LA21_N: J1.H26 (LA21_N), U7.6 (A4)
LA21_P: J1.H25 (LA21_P), U7.5 (A3)
LA22_N: J1.G25 (LA22_N), U7.4 (A2)
LA22_P: J1.G24 (LA22_P), U7.3 (A1)
LA23_N: J1.D24 (LA23_N), U3.6 (A4)
LA23_P: J1.D23 (LA23_P), U3.5 (A3)
LA24_N: J1.H29 (LA24_N), U7.10 (A8)
LA24_P: J1.H28 (LA24_P), U7.9 (A7)
LA25_N: J1.G28 (LA25_N), U7.8 (A6)
LA25_P: J1.G27 (LA25_P), U7.7 (A5)
LA26_N: J1.D27 (LA26_N), U3.10 (A8)
LA26_P: J1.D26 (LA26_P), U3.8 (A6)
LA27_N: J1.C27 (LA27_N), U3.9 (A7)
LA27_P: J1.C26 (LA27_P), U3.7 (A5)
LA28_N: J1.H32 (LA28_N)
LA28_P: J1.H31 (LA28_P)
LA29_N: J1.G31 (LA29_N), U8.4 (A2)
LA29_P: J1.G30 (LA29_P), U8.3 (A1)
LA30_N: J1.H35 (LA30_N)
LA30_P: J1.H34 (LA30_P)
LA31_N: J1.G34 (LA31_N)
LA31_P: J1.G33 (LA31_P)
LA32_N: J1.H38 (LA32_N)
LA32_P: J1.H37 (LA32_P)
LA33_N: J1.G37 (LA33_N)
LA33_P: J1.G36 (LA33_P)
LED_A: D2.2 (A), R73.2
NR: C59.1, U11.13 (NR/SS)
SB0: R57.1, U9.18 (1Y1)
SB1: R58.1, U9.16 (1Y2)
SB2: R59.1, U9.14 (1Y3)
SB3: R60.1, U9.12 (1Y4)
SB4: R61.1, U9.9 (2Y1)
SB5: R62.1, U9.7 (2Y2)
SB6: R63.1, U9.5 (2Y3)
SB7: R64.1, U9.3 (2Y4)
SB8: R65.1, U10.18 (1Y1)
SB9: R66.1, U10.16 (1Y2)
SB10: R67.1, U10.14 (1Y3)
SB11: R68.1, U10.12 (1Y4)
SB12: R69.1, U10.9 (2Y1)
SB13: R70.1, U10.7 (2Y2)
SB14: R71.1, U10.5 (2Y3)
SB15: R72.1, U10.3 (2Y4)
SCLK0: J2.8, R57.2
SCLK1: J3.8, R58.2
SCLK2: J4.8, R59.2
SCLK3: J5.8, R60.2
SCLK4: J6.8, R61.2
SCLK5: J7.8, R62.2
SCLK6: J8.8, R63.2
SCLK7: J9.8, R64.2
SCLK8: J10.8, R65.2
SCLK9: J11.8, R66.2
SCLK10: J12.8, R67.2
SCLK11: J13.8, R68.2
SCLK12: J14.8, R69.2
SCLK13: J15.8, R70.2
SCLK14: J16.8, R71.2
SCLK15: J17.8, R72.2
SCLK_A: U8.21 (B1), U9.2 (1A1), U9.4 (1A2), U9.6 (1A3), U9.8 (1A4), U9.11 (2A1), U9.13 (2A2), U9.15 (2A3), U9.17 (2A4)
SCLK_B: U8.20 (B2), U10.2 (1A1), U10.4 (1A2), U10.6 (1A3), U10.8 (1A4), U10.11 (2A1), U10.13 (2A2), U10.15 (2A3), U10.17 (2A4)
SDO0: J2.6, J3.6, R1.1, U7.21 (B1)
SDO1: J4.6, J5.6, R2.1, U7.20 (B2)
SDO2: J6.6, J7.6, R3.1, U7.19 (B3)
SDO3: J8.6, J9.6, R4.1, U7.18 (B4)
SDO4: J10.6, J11.6, R5.1, U7.17 (B5)
SDO5: J12.6, J13.6, R6.1, U7.16 (B6)
SDO6: J14.6, J15.6, R7.1, U7.15 (B7)
SDO7: J16.6, J17.6, R8.1, U7.14 (B8)
VADJ: C1.1, C3.1, C5.1, C7.1, C9.1, C11.1, C13.1, C15.1, C17.1, C18.1, J1.G39 (VADJ), J1.H40 (VADJ), TP4.1, U1.1 (VCCA), U1.2 (DIR), U2.1 (VCCA), U3.1 (VCCA), U4.1 (VCCA), U4.2 (DIR), U5.1 (VCCA), U6.1 (VCCA), U7.1 (VCCA), U8.1 (VCCA), U8.2 (DIR)
WAKE0: J2.7, R10.2, U2.21 (B1)
WAKE1: J3.7, R13.2, U2.20 (B2)
WAKE2: J4.7, R16.2, U2.19 (B3)
WAKE3: J5.7, R19.2, U2.18 (B4)
WAKE4: J6.7, R22.2, U2.17 (B5)
WAKE5: J7.7, R25.2, U2.16 (B6)
WAKE6: J8.7, R28.2, U2.15 (B7)
WAKE7: J9.7, R31.2, U2.14 (B8)
WAKE8: J10.7, R34.2, U5.21 (B1)
WAKE9: J11.7, R37.2, U5.20 (B2)
WAKE10: J12.7, R40.2, U5.19 (B3)
WAKE11: J13.7, R43.2, U5.18 (B4)
WAKE12: J14.7, R46.2, U5.17 (B5)
WAKE13: J15.7, R49.2, U5.16 (B6)
WAKE14: J16.7, R52.2, U5.15 (B7)
WAKE15: J17.7, R55.2, U5.14 (B8)

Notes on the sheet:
16-channel backplane for the ADS7057 channel cards
One board. The FMC plug (ZedBoard LPC) is on the left. Eight SN74LVC8T245 level shifters (A side VADJ, any of 1.8 / 2.5 / 3.3 V; B side the board's 3.3 V) feed a 4 x 4 matrix of vertical 2x6 sockets. Slot k = 4 * row + column.
58 lines: 18 outputs (16 CS, 2 SCLK), 40 inputs (16 WAKE_N, 16 BIG_N, 8 SDO lanes; slots 2j and 2j+1 share lane j). SCLK of slots 0-7 and 8-15 each pass a SN74LVC244A with 22 R per branch. 100 k pull-ups keep CS, WAKE_N and BIG_N high on an empty slot.
Socket pads are not the card pin numbers (the header rows swap): card pin 1 CS -> pad 2, pin 2 BIG_N -> pad 1, pin 5 SDO -> pad 6, pin 7 SCLK -> pad 8, pin 8 WAKE_N -> pad 7. Insert each card with its components facing +X. PRSNT_M2C_L grounded, TDI tied to TDO.

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
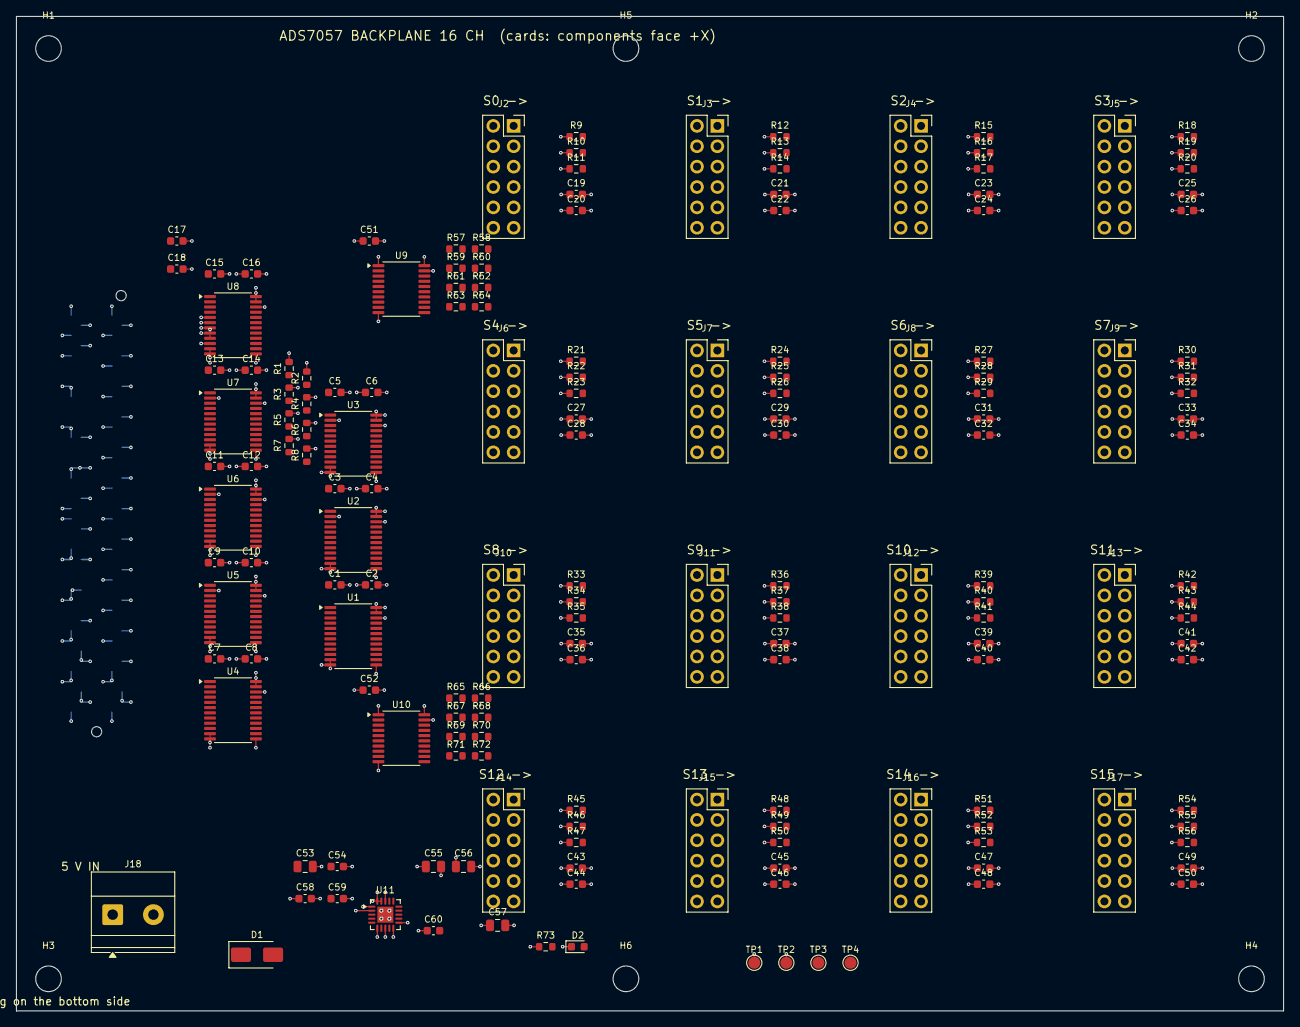
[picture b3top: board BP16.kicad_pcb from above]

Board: 6 copper layers, 158.0 x 124.0 mm, 174 parts (1 on the bottom side), 157 nets.
